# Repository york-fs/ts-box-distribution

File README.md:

# TS Box Distribution Board

The TS box distribution board lives in the high voltage TS box enclosure and supply LVS power and signals to the
energy meter, discharge relay, and the interlock of the high voltage disconnect.

[Latest Release](https://github.com/york-fs/ts-box-distribution/releases/latest)
[Interactive BOM](https://york-fs.github.io/ts-box-distribution/ibom.html)

## Cloning

A recursive clone must be used to download the `kicad-library` repository:

    git clone --recursive https://github.com/york-fs/ts-box-distribution.git

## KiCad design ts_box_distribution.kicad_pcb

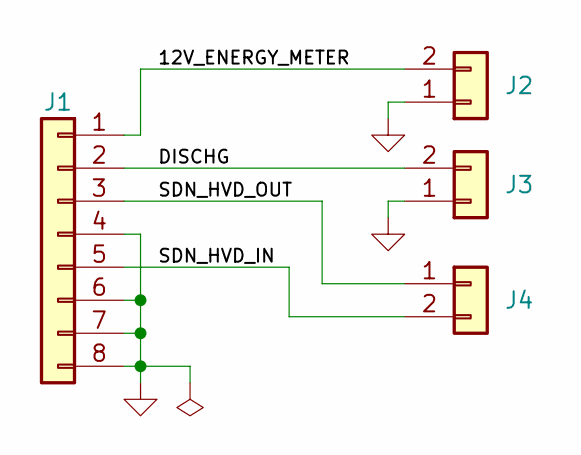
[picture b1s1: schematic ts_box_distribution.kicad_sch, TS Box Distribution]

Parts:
J1: Conn_01x08; AMPSEAL-8-776280; Mfr # 776280-1; DigiKey # 776280-1-ND
J2: Conn_01x02; MolexMicrofitPlus1x2; Mfr # 2157601022; DigiKey # 900-2157601022-ND
J3: Conn_01x02; MolexMicrofitPlus1x2; Mfr # 2157601002; DigiKey # 900-2157601002-ND
J4: Conn_01x02; MolexMicrofitPlus1x2; Mfr # 2157601032; DigiKey # 900-2157601032-ND

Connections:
/12V_ENERGY_METER: J1.1, J2.2
/DISCHG: J1.2, J3.2
/SDN_HVD_IN: J1.5, J4.2
/SDN_HVD_OUT: J1.3, J4.1
GND: J1.4, J1.6, J1.7, J1.8, J2.1, J3.1

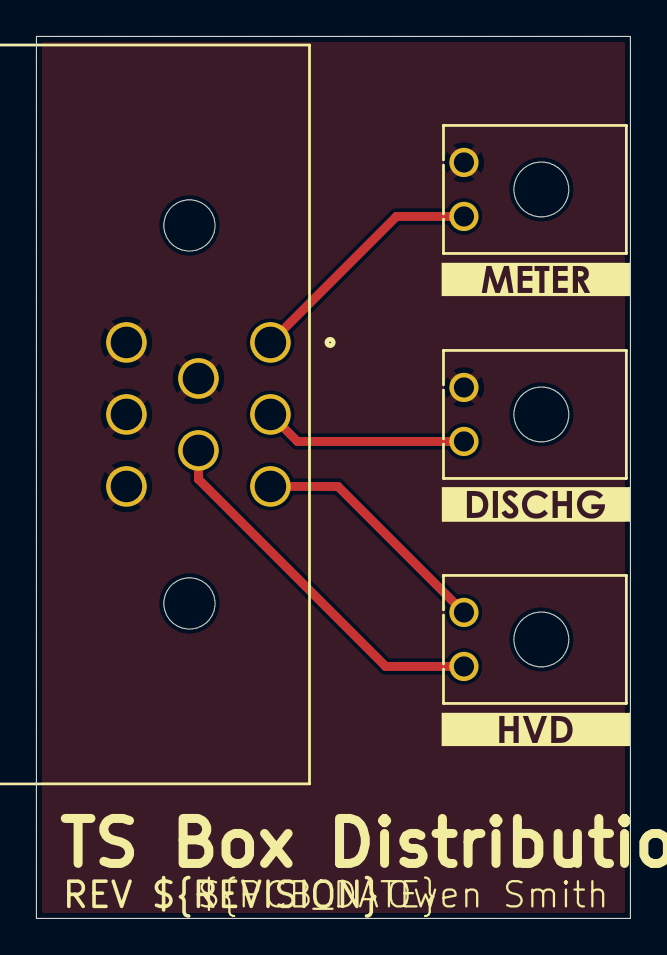
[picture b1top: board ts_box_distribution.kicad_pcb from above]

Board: 2 copper layers, 33.0 x 49.0 mm, 7 parts (0 on the bottom side), 5 nets.

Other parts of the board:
kibuzzard-6A2049B2: G***; kibuzzard-6A2049B2
kibuzzard-6A20499C: G***; kibuzzard-6A20499C
kibuzzard-6A204969: G***; kibuzzard-6A204969

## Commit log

2026-06-26 ci: Add KiCad CI
2026-06-26 meta: Add README
2026-06-26 schematic: Fill out BOM
